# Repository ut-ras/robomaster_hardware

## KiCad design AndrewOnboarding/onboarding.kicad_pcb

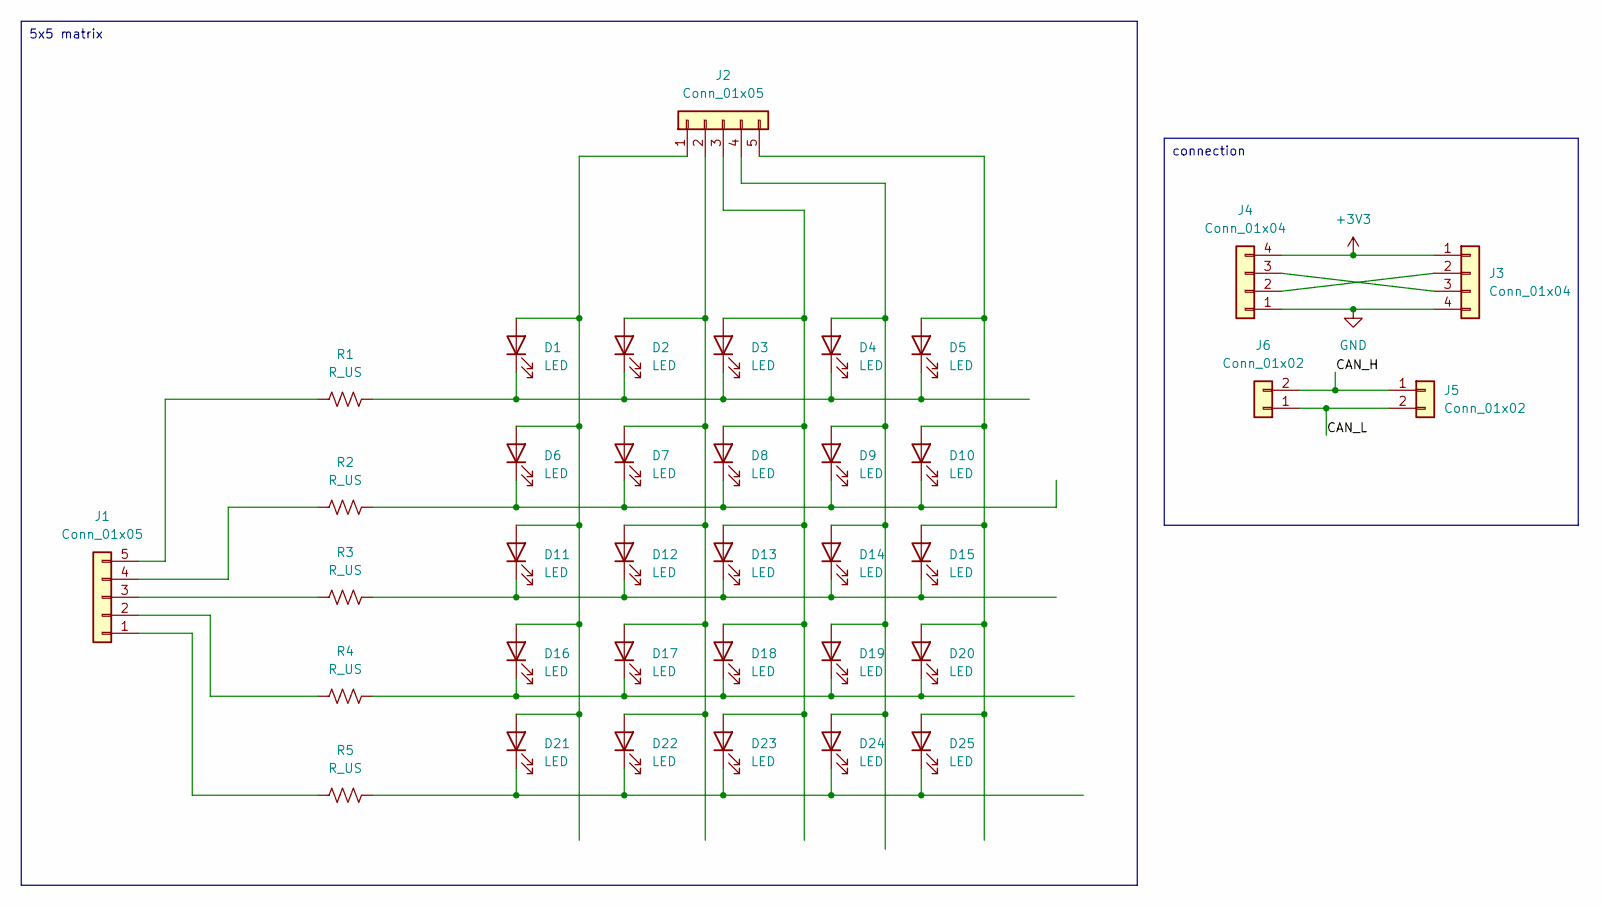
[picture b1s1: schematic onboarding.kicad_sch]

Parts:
D1, D2, D3, D4, D5, D6, D7, D8, D9, D10, D11, D12, D13, D14, D15, D16, D17, D18, D19, D20, D21, D22, D23, D24, D25: LED; LED_D3.0mm
J1, J2: Conn_01x05; PinHeader_1x05_P2.54mm_Vertical
J3, J4: Conn_01x04; JST_NV_B04P-NV_1x04_P5.00mm_Vertical
J5, J6: Conn_01x02; JST_NV_B02P-NV_1x02_P5.00mm_Vertical
R1, R2, R3, R4, R5: R_US; R_Axial_DIN0207_L6.3mm_D2.5mm_P7.62mm_Horizontal

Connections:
+3V3: J3.1, J4.4
/CAN_H: J5.1, J6.2
/CAN_L: J5.2, J6.1
GND: J3.4, J4.1
unnamed: D1.2 (A), D6.2 (A), D11.2 (A), D16.2 (A), D21.2 (A), J2.1
unnamed: D1.1 (K), D2.1 (K), D3.1 (K), D4.1 (K), D5.1 (K), R1.1
unnamed: D5.2 (A), D10.2 (A), D15.2 (A), D20.2 (A), D25.2 (A), J2.5
unnamed: D6.1 (K), D7.1 (K), D8.1 (K), D9.1 (K), D10.1 (K), R2.2
unnamed: D11.1 (K), D12.1 (K), D13.1 (K), D14.1 (K), D15.1 (K), R3.1
unnamed: D2.2 (A), D7.2 (A), D12.2 (A), D17.2 (A), D22.2 (A), J2.2
unnamed: D3.2 (A), D8.2 (A), D13.2 (A), D18.2 (A), D23.2 (A), J2.3
unnamed: D4.2 (A), D9.2 (A), D14.2 (A), D19.2 (A), D24.2 (A), J2.4
unnamed: D16.1 (K), D17.1 (K), D18.1 (K), D19.1 (K), D20.1 (K), R4.1
unnamed: D21.1 (K), D22.1 (K), D23.1 (K), D24.1 (K), D25.1 (K), R5.1
unnamed: J1.1, R5.2
unnamed: J1.2, R4.2
unnamed: J1.3, R3.2
unnamed: J1.4, R2.1
unnamed: J1.5, R1.2
unnamed: J3.2, J4.2
unnamed: J3.3, J4.3

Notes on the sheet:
5x5 matrix
connection

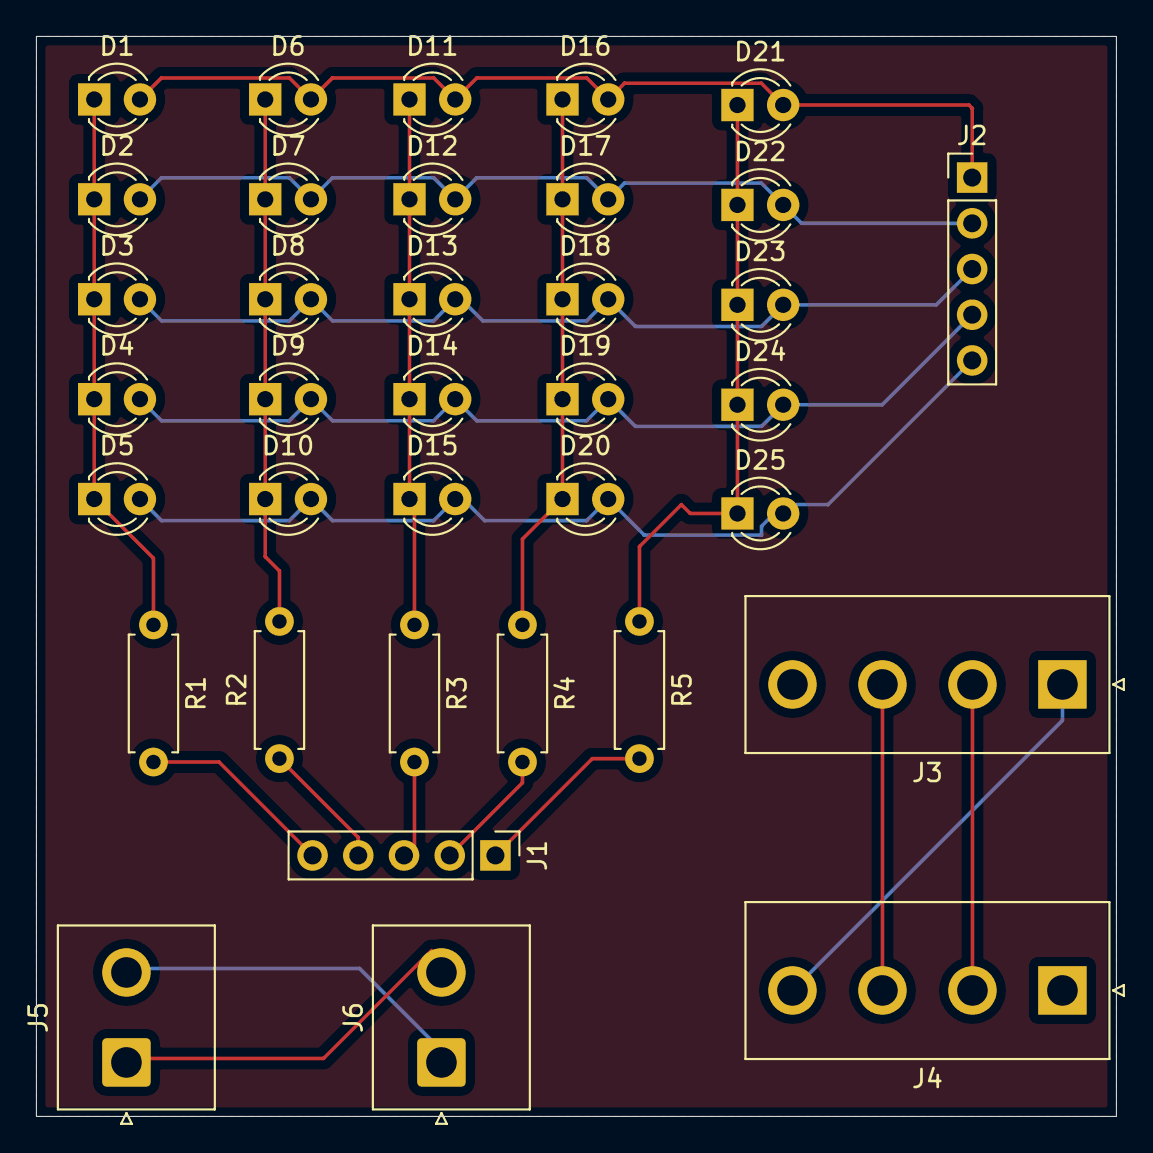
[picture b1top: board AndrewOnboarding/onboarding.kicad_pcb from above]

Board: 2 copper layers, 60.0 x 60.0 mm, 36 parts (0 on the bottom side), 21 nets.

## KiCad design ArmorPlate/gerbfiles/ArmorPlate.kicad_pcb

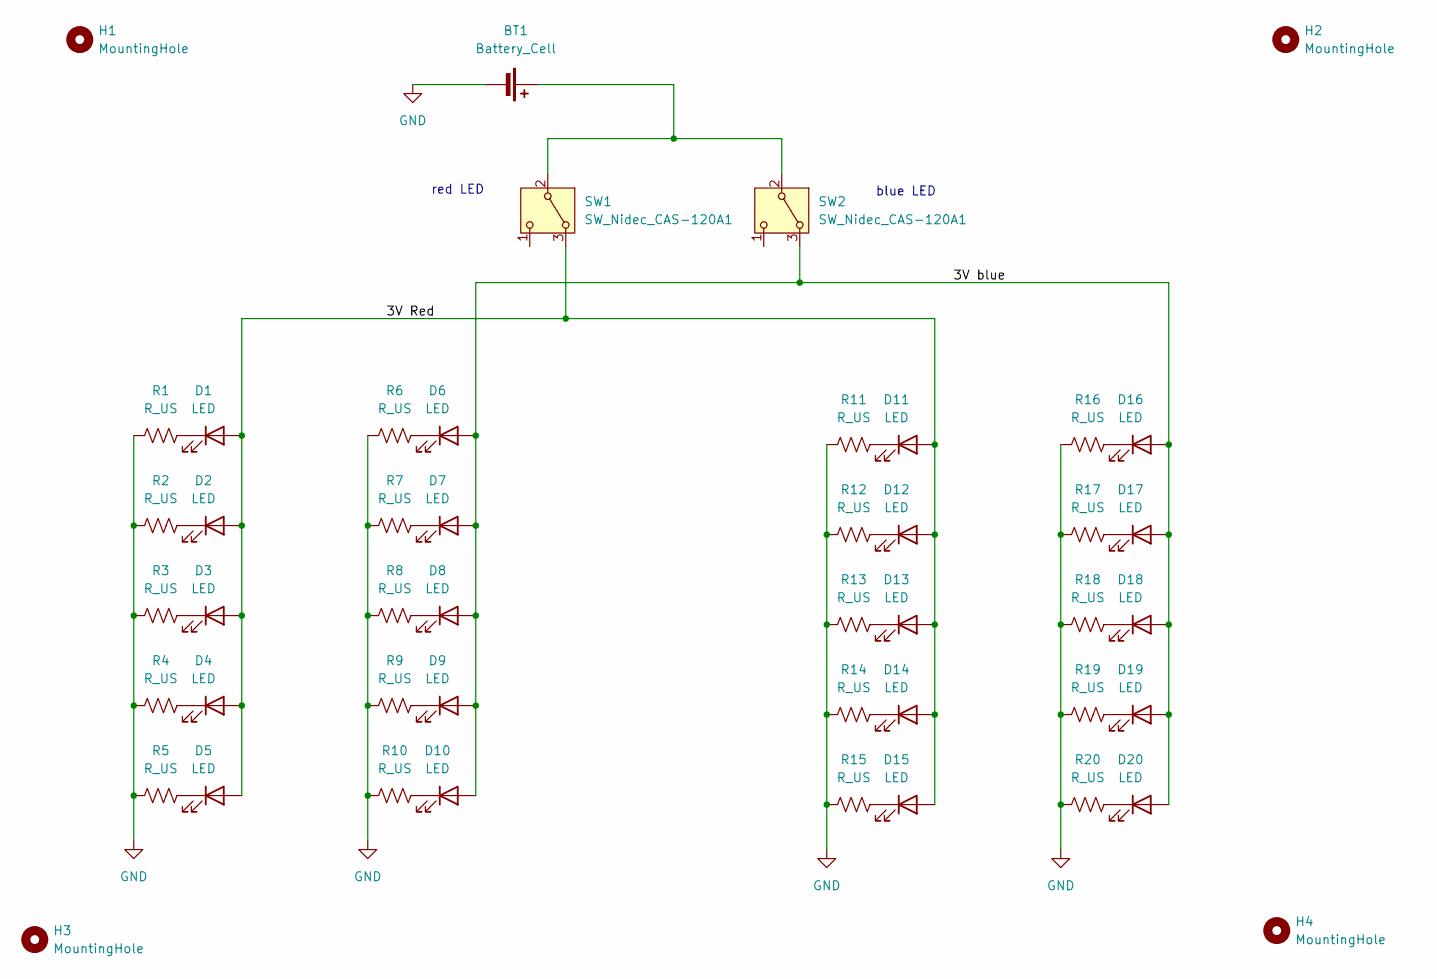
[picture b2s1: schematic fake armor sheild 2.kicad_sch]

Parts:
BT1: Battery_Cell; BatteryHolder_Keystone_2468_2xAAA; Mouser Part Number 613-MN1500-144
D1, D2, D3, D4, D5, D6, D7, D8, D9, D10, D11, D12, D13, D14, D15, D16, D17, D18, D19, D20: LED; LED_0603_1608Metric_Pad1.05x0.95mm_HandSolder; Mouser Part Number 710-150060SS75000
H1, H2, H3, H4: MountingHole; MountingHole_4.5mm
R1, R2, R3, R4, R5, R6, R7, R8, R9, R10, R11, R12, R13, R14, R15, R16, R17, R18, R19, R20: R_US; R_0603_1608Metric_Pad0.98x0.95mm_HandSolder; Mouser Part Number 71-WSLP25125L000FEA
SW1, SW2: SW_Nidec_CAS-120A1; SW_Push_2P1T_Toggle_CK_PVA1xxH1xxxxxxV2; Mouser Part Number 611-181D01000

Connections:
/3V Red: D1.2 (A), D2.2 (A), D3.2 (A), D4.2 (A), D5.2 (A), D11.2 (A), D12.2 (A), D13.2 (A), D14.2 (A), D15.2 (A), SW1.3 (A); also elsewhere on the board
/3V blue: D6.2 (A), D7.2 (A), D8.2 (A), D9.2 (A), D10.2 (A), D16.2 (A), D17.2 (A), D18.2 (A), D19.2 (A), D20.2 (A), SW2.3 (A); also elsewhere on the board
GND: BT1.2 (-), R1.1, R2.1, R3.1, R4.1, R5.1, R6.1, R7.1, R8.1, R9.1, R10.1, R11.1, R12.1, R13.1, R14.1, R15.1, R16.1, R17.1, R18.1, R19.1, R20.1
unnamed 3: BT1.1 (+), SW1.2 (B), SW2.2 (B); also elsewhere on the board
unnamed: D1.1 (K), R1.2
unnamed: D2.1 (K), R2.2
unnamed: D3.1 (K), R3.2
unnamed: D4.1 (K), R4.2
unnamed: D5.1 (K), R5.2
unnamed: D6.1 (K), R6.2
unnamed: D7.1 (K), R7.2
unnamed: D8.1 (K), R8.2
unnamed: D9.1 (K), R9.2
unnamed: D10.1 (K), R10.2
unnamed: D11.1 (K), R11.2
unnamed: D12.1 (K), R12.2
unnamed: D13.1 (K), R13.2
unnamed: D14.1 (K), R14.2
unnamed: D15.1 (K), R15.2
unnamed: D16.1 (K), R16.2
unnamed: D17.1 (K), R17.2
unnamed: D18.1 (K), R18.2
unnamed: D19.1 (K), R19.2
unnamed: D20.1 (K), R20.2

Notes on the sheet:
blue LED
red LED

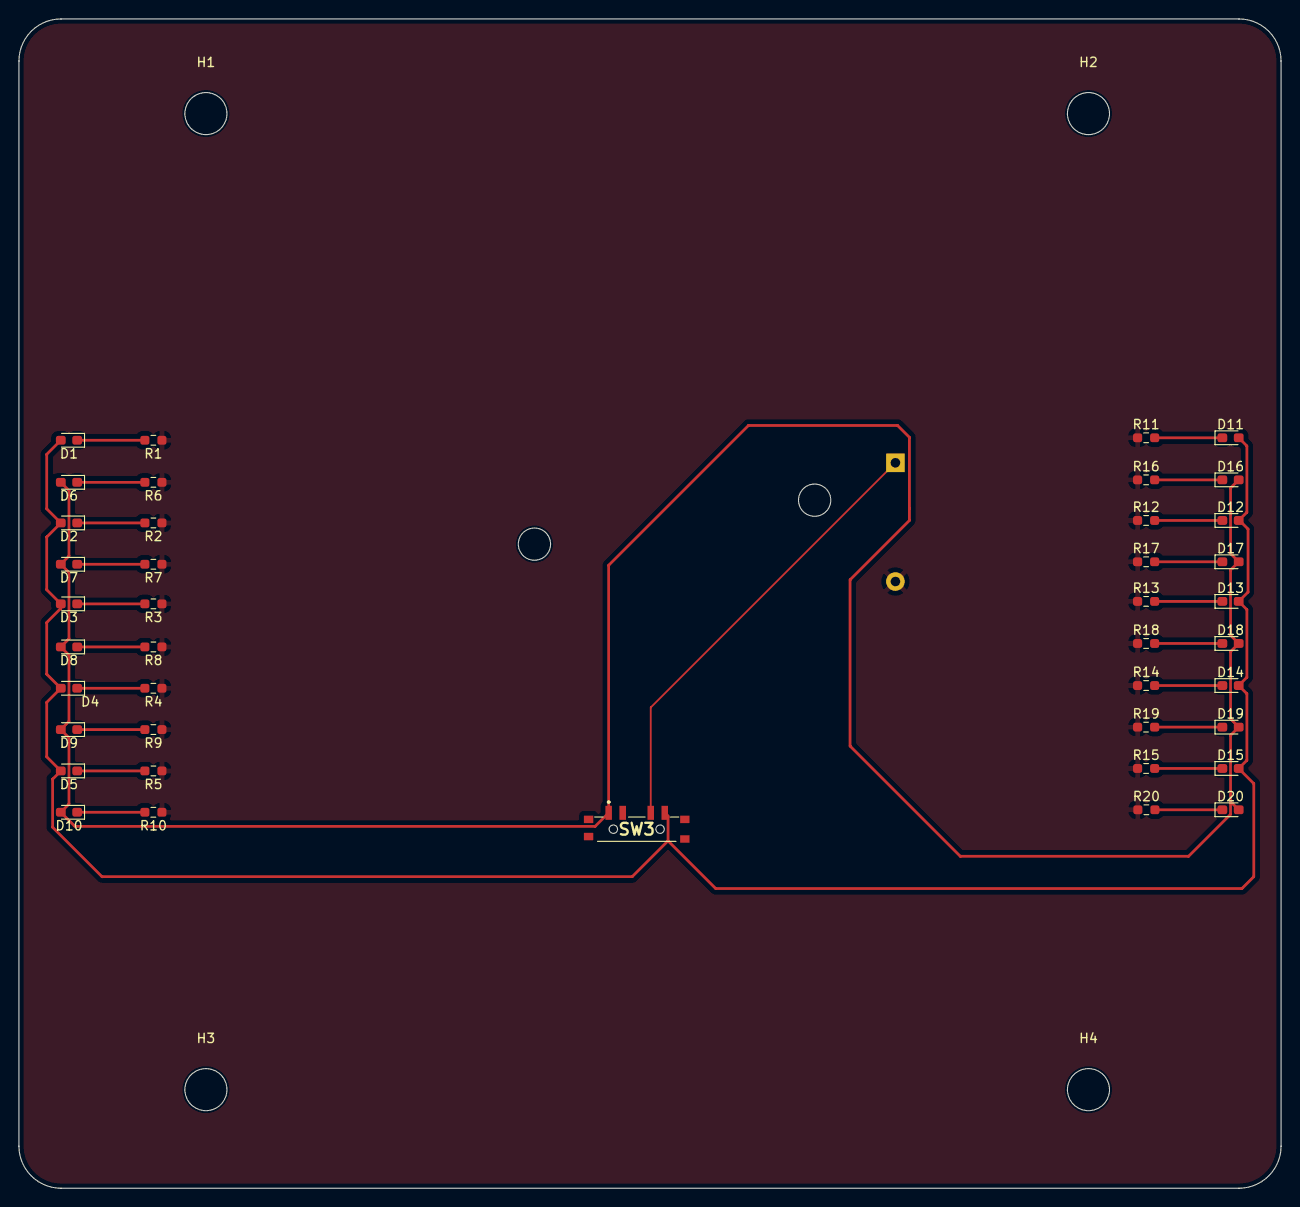
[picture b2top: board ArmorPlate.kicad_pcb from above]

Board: 2 copper layers, 135.0 x 125.1 mm, 46 parts (1 on the bottom side), 24 nets.

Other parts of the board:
SW3: SW_SP3T; EG1315AA

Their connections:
/3V Red: SW3.4; also elsewhere on the board
/3V blue: SW3.1; also elsewhere on the board
unnamed 3: SW3.3; also elsewhere on the board

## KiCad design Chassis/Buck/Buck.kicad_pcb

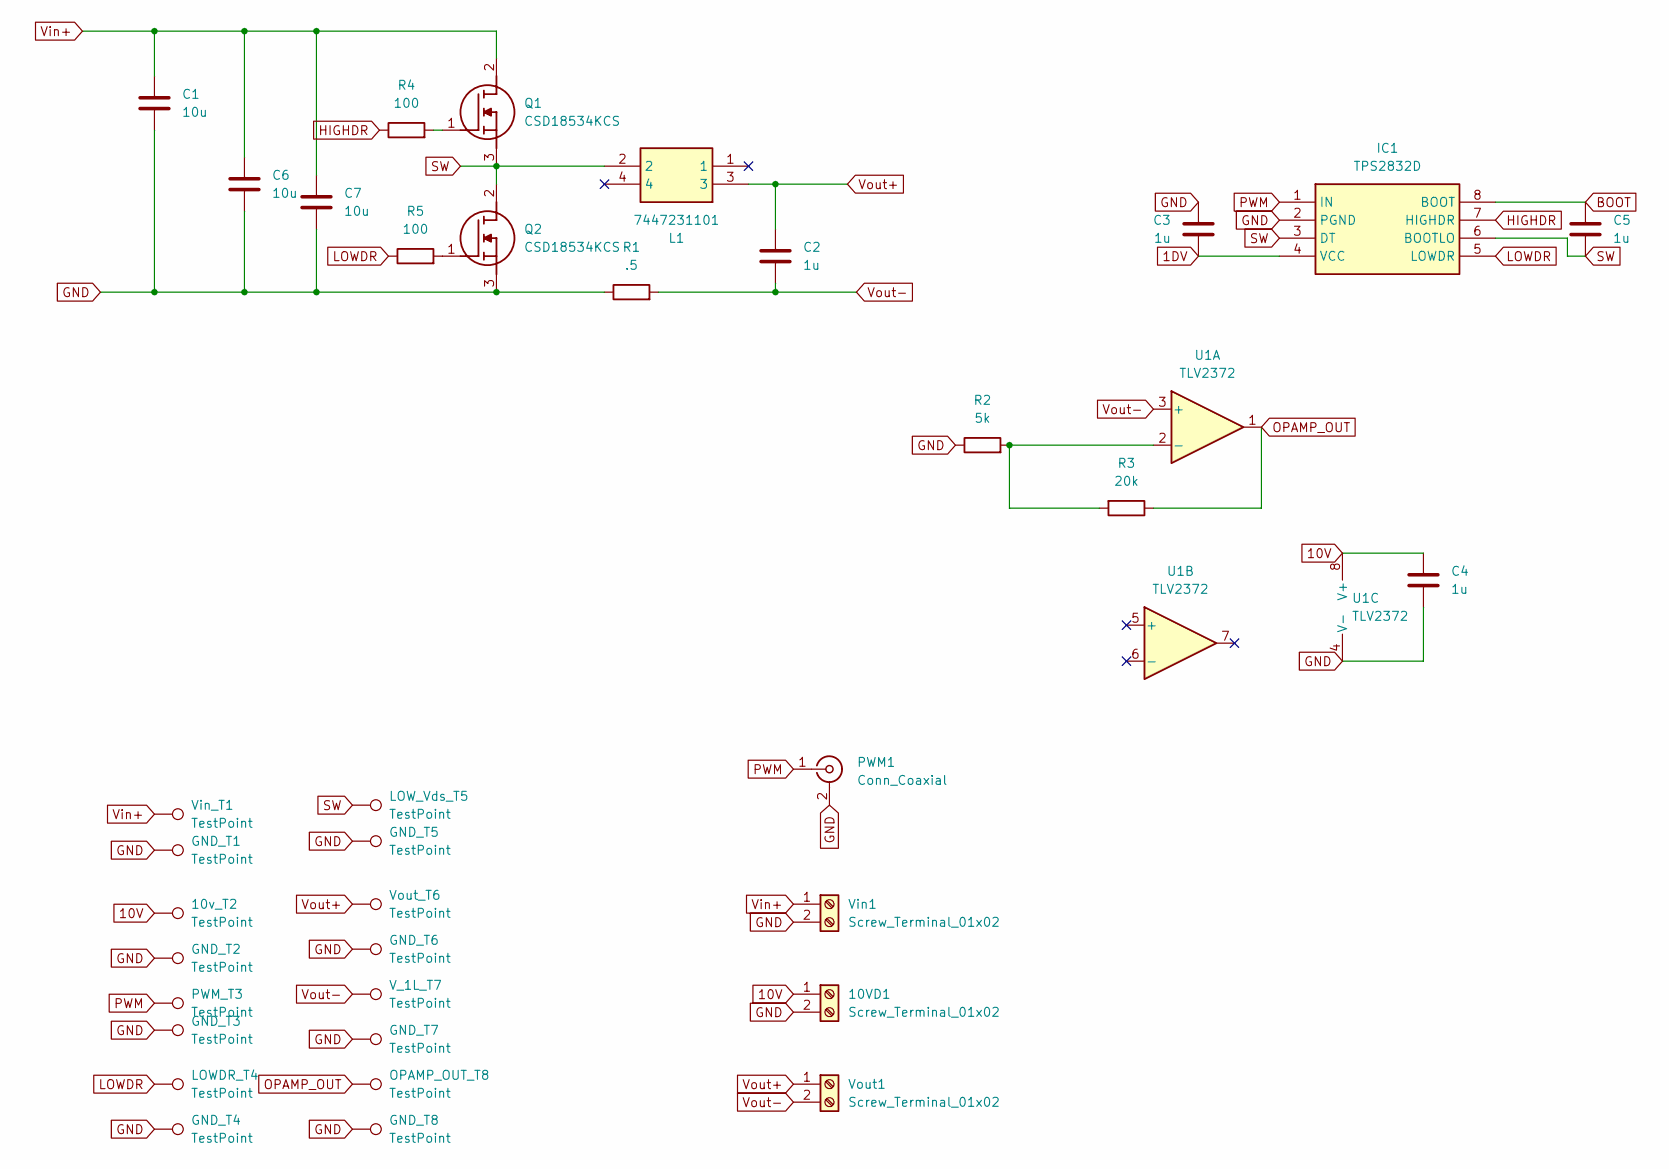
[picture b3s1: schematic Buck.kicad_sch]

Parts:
10VD1: Screw_Terminal_01x02; TO-220-3_Vertical
10v_T2: TestPoint; TestPoint_Keystone_5010-5014_Multipurpose
C1, C6, C7: 10u; C_Disc_D3.8mm_W2.6mm_P2.50mm
C2, C3, C4, C5: 1u; C_Disc_D3.8mm_W2.6mm_P2.50mm
GND_T1, GND_T2, GND_T3, GND_T4, GND_T5, GND_T6, GND_T7, GND_T8: TestPoint; TestPoint_Keystone_5010-5014_Multipurpose
IC1: TPS2832D; SO-8_3.9x4.9mm_P1.27mm; Manufacturer_Part_Number TPS2832D; Mouser Part Number 595-TPS2832D
L1: 7447231101; Manufacturer_Part_Number 7447231101
LOWDR_T4: TestPoint; TestPoint_Keystone_5010-5014_Multipurpose
LOW_Vds_T5: TestPoint; TestPoint_Keystone_5010-5014_Multipurpose
OPAMP_OUT_T8: TestPoint; TestPoint_Keystone_5010-5014_Multipurpose
PWM1: Conn_Coaxial; BNC_Amphenol_B6252HB-NPP3G-50_Horizontal
PWM_T3: TestPoint; TestPoint_Keystone_5010-5014_Multipurpose
Q1, Q2: CSD18534KCS; TO-220-3_Vertical; Manufacturer_Part_Number CSD18534KCS; Mouser Part Number 595-CSD18534KCS
R1: .5; R_Axial_DIN0922_L20.0mm_D9.0mm_P30.48mm_Horizontal
R2: 5k; R_Axial_DIN0207_L6.3mm_D2.5mm_P10.16mm_Horizontal
R3: 20k; R_Axial_DIN0207_L6.3mm_D2.5mm_P10.16mm_Horizontal
R4, R5: 100; R_Axial_DIN0207_L6.3mm_D2.5mm_P10.16mm_Horizontal
U1: TLV2372; SO-8_3.9x4.9mm_P1.27mm
V_1L_T7: TestPoint; TestPoint_Keystone_5010-5014_Multipurpose
Vin1: Screw_Terminal_01x02; PhoenixContact_MSTBA_2,5_2-G_1x02_P5.00mm_Horizontal
Vin_T1: TestPoint; TestPoint_Keystone_5010-5014_Multipurpose
Vout1: Screw_Terminal_01x02; PhoenixContact_MSTBA_2,5_2-G_1x02_P5.00mm_Horizontal
Vout_T6: TestPoint; TestPoint_Keystone_5010-5014_Multipurpose

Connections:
1DV: C3.2, IC1.4 (VCC)
10V: 10VD1.1, 10v_T2.1, C4.1, U1.8 (V+)
BOOT: C5.1, IC1.8 (BOOT)
GND: 10VD1.2, C1.1, C3.1, C4.2, C6.2, C7.2, GND_T1.1, GND_T2.1, GND_T3.1, GND_T4.1, GND_T5.1, GND_T6.1, GND_T7.1, GND_T8.1, IC1.2 (PGND), PWM1.2 (Ext), Q2.3 (S), R1.1, R2.1, U1.4 (V-), Vin1.2
HIGHDR: IC1.7 (HIGHDR), R4.1
LOWDR: IC1.5 (LOWDR), LOWDR_T4.1, R5.1
unnamed: Q1.1 (G), R4.2
unnamed: Q2.1 (G), R5.2
unnamed: R2.2, R3.2, U1.2 (-)
OPAMP_OUT: OPAMP_OUT_T8.1, R3.1, U1.1
PWM: IC1.1 (IN), PWM1.1 (In), PWM_T3.1
SW: C5.2, IC1.3 (DT), IC1.6 (BOOTLO), L1.2, LOW_Vds_T5.1, Q1.3 (S), Q2.2 (D)
Vin+: C1.2, C6.1, C7.1, Q1.2 (D), Vin1.1, Vin_T1.1
Vout+: C2.1, L1.3, Vout1.1, Vout_T6.1
Vout-: C2.2, R1.2, U1.3 (+), V_1L_T7.1, Vout1.2

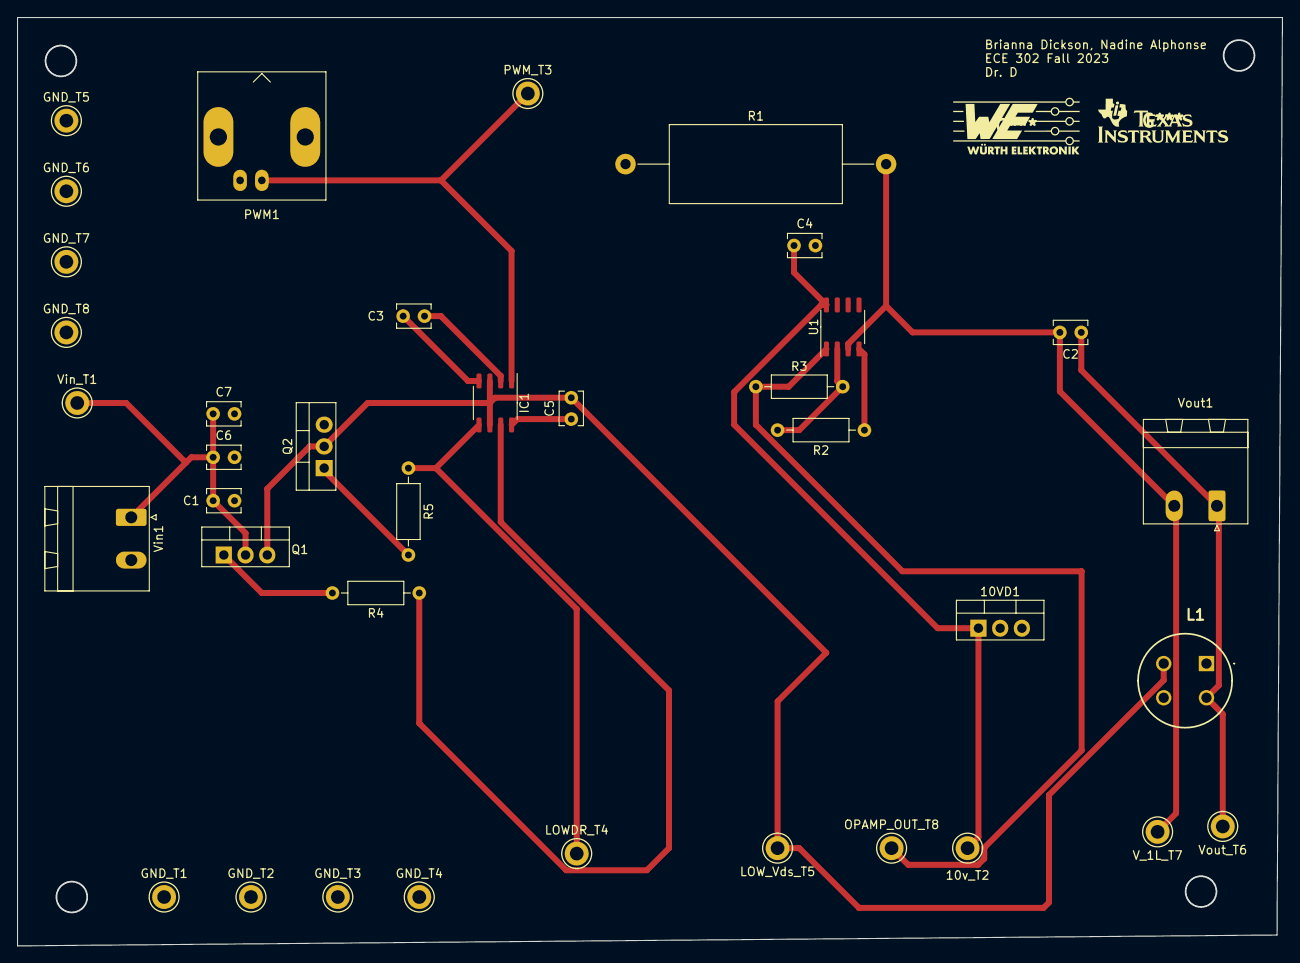
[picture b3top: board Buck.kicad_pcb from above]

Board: 2 copper layers, 148.0 x 108.6 mm, 37 parts (0 on the bottom side), 15 nets.

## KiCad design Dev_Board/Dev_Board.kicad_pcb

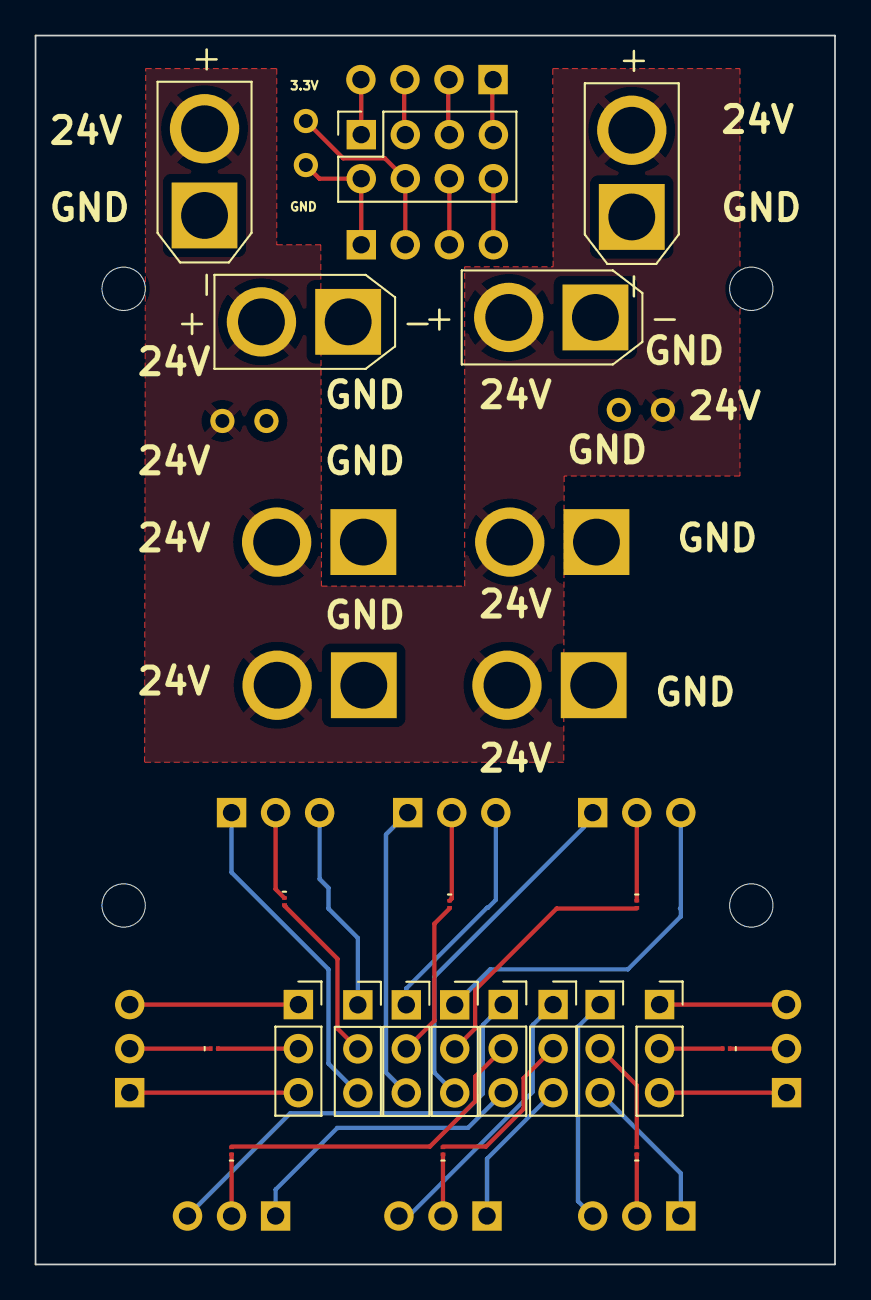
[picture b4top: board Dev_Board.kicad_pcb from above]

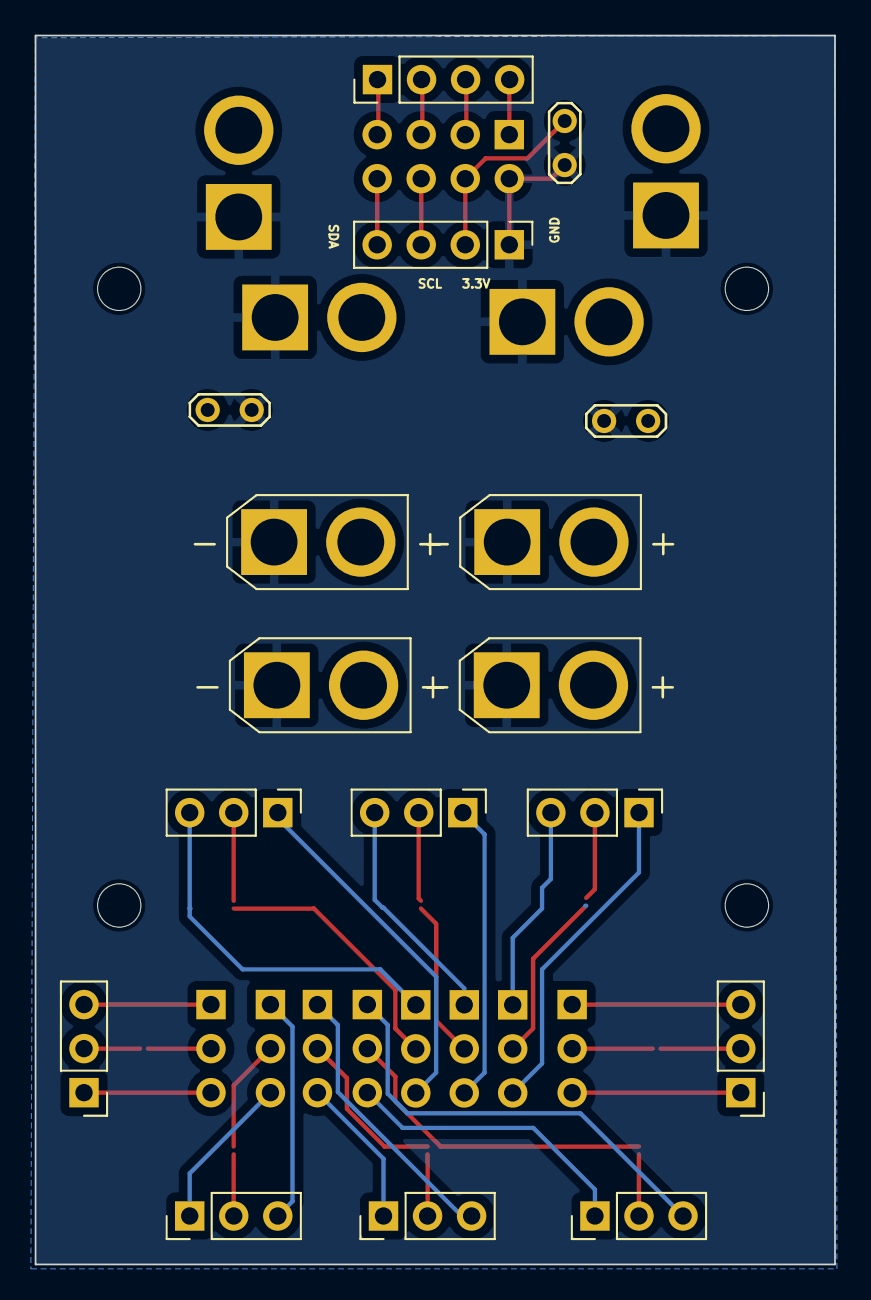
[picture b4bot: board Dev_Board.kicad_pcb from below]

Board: 2 copper layers, 46.1 x 70.9 mm, 42 parts (17 on the bottom side), 40 nets.

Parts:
D1, D4, D7, D11, D14, D17, D20, D23: D; Nexperia_DSN0603-2_0.6x0.3mm_P0.4mm
DBUS1: Conn_01x03; PinSocket_1x03_P2.54mm_Vertical
H1, H2, H3, H4: MountingHole; MountingHole_2.5mm
IO_Port1: Conn_02x04_Odd_Even; PinSocket_2x04_P2.54mm_Vertical
In_Port1, In_Port2: Conn_01x02; AMASS_XT30U-F_1x02_P5.0mm_Vertical
J1, J2: Conn_01x04; PinHeader_1x04_P2.54mm_Vertical
Out_Port1, Out_Port2, Out_Port3, Out_Port4, Out_Port6, Out_Port8: Conn_01x02; AMASS_XT30U-F_1x02_P5.0mm_Vertical
PWM_R1, PWM_R2, PWM_R3, PWM_R4, PWM_R5, PWM_R6, PWM_R7: Conn_01x03; PinSocket_1x03_P2.54mm_Vertical
PWM_R8, PWM_R9, PWM_R10, PWM_R11, PWM_R12, PWM_R13, PWM_R14, PWM_R15: Conn_01x03; PinHeader_1x03_P2.54mm_Vertical
TP1, TP4, TP5: TestPoint_2Pole; TestPoint_2Pads_Pitch2.54mm_Drill0.8mm

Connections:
+3.3V: IO_Port1.4, J2.2, TP1.2
+24V: In_Port1.2, In_Port2.2, Out_Port1.2, Out_Port2.2, Out_Port3.2, Out_Port4.2, Out_Port6.2, Out_Port8.2, TP4.2, TP5.2
/A2: PWM_R2.1, PWM_R9.3
/A3: PWM_R3.1, PWM_R10.3
/A4: PWM_R4.1, PWM_R11.3
/A5: PWM_R5.1, PWM_R12.3
/A6: PWM_R6.1, PWM_R13.3
/B1 (5V): D1.2 (A), PWM_R1.2
/B3: D7.2 (A), PWM_R3.2
/B4: D11.2 (A), PWM_R4.2
/B5: D14.2 (A), PWM_R5.2
/B6: D17.2 (A), PWM_R6.2
/C3: PWM_R3.3, PWM_R10.1
/C4: PWM_R4.3, PWM_R11.1
/C5: PWM_R5.3, PWM_R12.1
/C8: DBUS1.3, PWM_R15.1
/I2C2_SCL: IO_Port1.6, J2.3
/I2C2_SDA: IO_Port1.8, J2.4
/SPI2_CLK: IO_Port1.3, J1.3
/SPI2_CS: IO_Port1.1, J1.4
/SPI2_MOSI: IO_Port1.5, J1.2
GND: IO_Port1.2, In_Port1.1, In_Port2.1, J2.1, Out_Port1.1, Out_Port2.1, Out_Port3.1, Out_Port4.1, Out_Port6.1, Out_Port8.1, TP1.1, TP4.1, TP5.1
unnamed: D1.1 (K), PWM_R8.2
unnamed: D4.2 (A), PWM_R2.2
unnamed: D4.1 (K), PWM_R9.2
unnamed: D7.1 (K), PWM_R10.2
unnamed: D11.1 (K), PWM_R11.2
unnamed: D14.1 (K), PWM_R12.2
unnamed: D17.1 (K), PWM_R13.2
unnamed: D20.2 (A), PWM_R7.2
unnamed: D20.1 (K), PWM_R14.2
unnamed: D23.2 (A), DBUS1.2
unnamed: D23.1 (K), PWM_R15.2
unnamed: DBUS1.1, PWM_R15.3
unnamed: PWM_R1.1, PWM_R8.3
unnamed: PWM_R1.3, PWM_R8.1
unnamed: PWM_R2.3, PWM_R9.1
unnamed: PWM_R6.3, PWM_R13.1
unnamed: PWM_R7.3, PWM_R14.1
unnamed: PWM_R7.1, PWM_R14.3

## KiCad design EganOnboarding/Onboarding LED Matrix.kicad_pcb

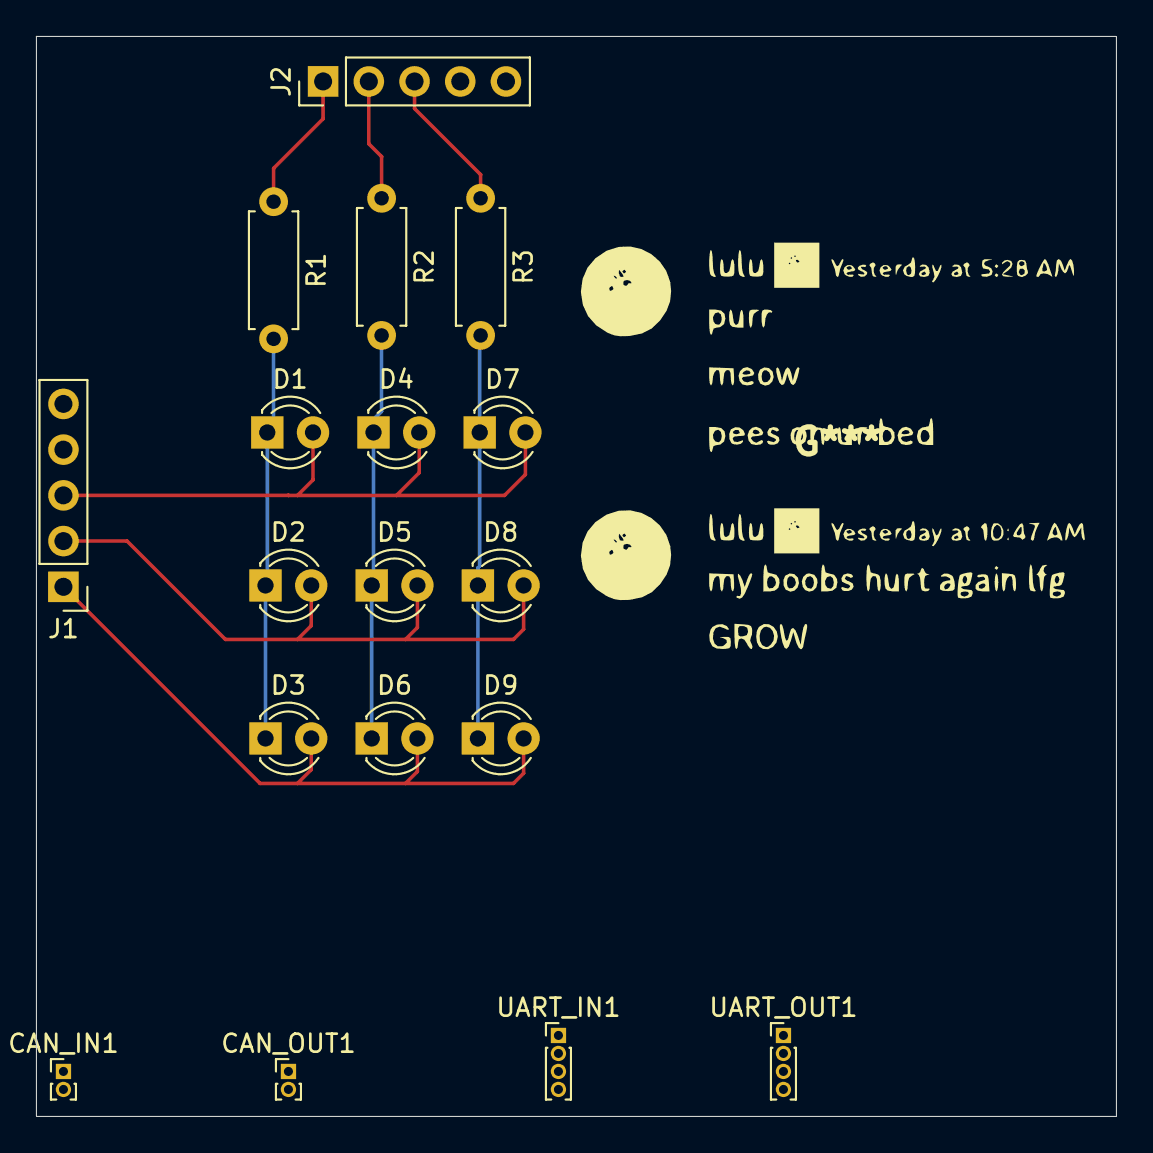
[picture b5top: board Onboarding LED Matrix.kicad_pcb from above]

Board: 2 copper layers, 60.0 x 60.0 mm, 18 parts (0 on the bottom side), 9 nets.

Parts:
CAN_IN1: Conn_01x02_Pin; PinHeader_1x02_P1.00mm_Vertical
CAN_OUT1: Conn_01x02_Pin; PinHeader_1x02_P1.00mm_Vertical
D1, D2, D3, D4, D5, D6, D7, D8, D9: LED; LED_D3.0mm
J1, J2: Conn_01x05_Pin; PinHeader_1x05_P2.54mm_Vertical
R1, R2, R3: R; R_Axial_DIN0207_L6.3mm_D2.5mm_P7.62mm_Horizontal
UART_IN1: Conn_01x04_Pin; PinHeader_1x04_P1.00mm_Vertical
UART_OUT1: Conn_01x04_Pin; PinHeader_1x04_P1.00mm_Vertical

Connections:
unnamed: D1.2 (A), D4.2 (A), D7.2 (A), J1.3
unnamed: D1.1 (K), D2.1 (K), D3.1 (K), R1.2
unnamed: D2.2 (A), D5.2 (A), D8.2 (A), J1.2
unnamed: D3.2 (A), D6.2 (A), D9.2 (A), J1.1
unnamed: D4.1 (K), D5.1 (K), D6.1 (K), R2.2
unnamed: D7.1 (K), D8.1 (K), D9.1 (K), R3.2
unnamed: J2.1, R1.1
unnamed: J2.2, R2.1
unnamed: J2.3, R3.1

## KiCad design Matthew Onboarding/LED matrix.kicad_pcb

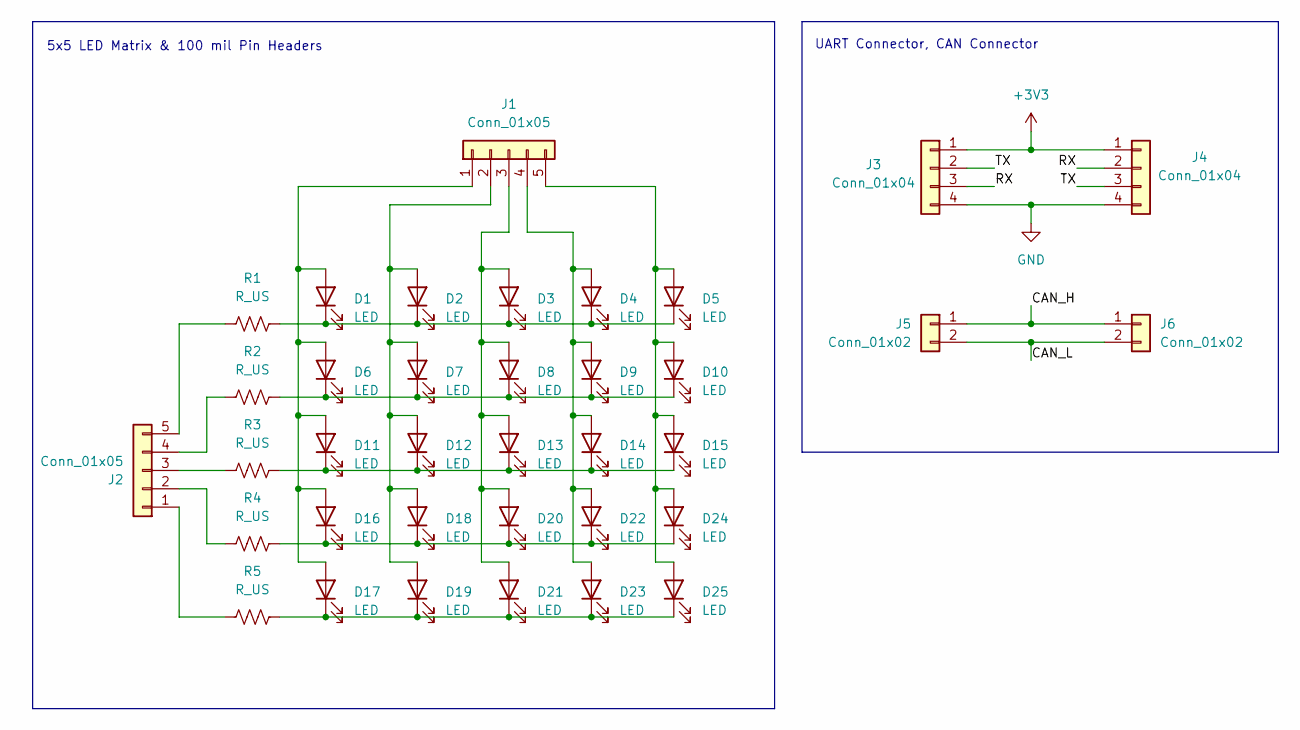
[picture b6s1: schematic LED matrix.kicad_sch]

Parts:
D1, D2, D3, D4, D5, D6, D7, D8, D9, D10, D11, D12, D13, D14, D15, D16, D17, D18, D19, D20, D21, D22, D23, D24, D25: LED; LED_D3.0mm
J1, J2: Conn_01x05; PinSocket_1x05_P2.54mm_Vertical
J3, J4: Conn_01x04; JST_GH_BM04B-GHS-TBT_1x04-1MP_P1.25mm_Vertical
J5, J6: Conn_01x02; JST_GH_BM02B-GHS-TBT_1x02-1MP_P1.25mm_Vertical
R1, R2, R3, R4, R5: R_US; R_Axial_DIN0207_L6.3mm_D2.5mm_P7.62mm_Horizontal

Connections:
+3V3: J3.1, J4.1
/CAN_H: J5.1, J6.1
/CAN_L: J5.2, J6.2
/RX: J3.3, J4.2
/TX: J3.2, J4.3
GND: J3.4, J4.4
unnamed: D1.2 (A), D6.2 (A), D11.2 (A), D16.2 (A), D17.2 (A), J1.1
unnamed: D1.1 (K), D2.1 (K), D3.1 (K), D4.1 (K), D5.1 (K), R1.2
unnamed: D5.2 (A), D10.2 (A), D15.2 (A), D24.2 (A), D25.2 (A), J1.5
unnamed: D6.1 (K), D7.1 (K), D8.1 (K), D9.1 (K), D10.1 (K), R2.2
unnamed: D11.1 (K), D12.1 (K), D13.1 (K), D14.1 (K), D15.1 (K), R3.2
unnamed: D2.2 (A), D7.2 (A), D12.2 (A), D18.2 (A), D19.2 (A), J1.2
unnamed: D3.2 (A), D8.2 (A), D13.2 (A), D20.2 (A), D21.2 (A), J1.3
unnamed: D4.2 (A), D9.2 (A), D14.2 (A), D22.2 (A), D23.2 (A), J1.4
unnamed: D16.1 (K), D18.1 (K), D20.1 (K), D22.1 (K), D24.1 (K), R4.2
unnamed: D17.1 (K), D19.1 (K), D21.1 (K), D23.1 (K), D25.1 (K), R5.2
unnamed: J2.1, R5.1
unnamed: J2.2, R4.1
unnamed: J2.3, R3.1
unnamed: J2.4, R2.1
unnamed: J2.5, R1.1

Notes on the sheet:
UART Connector, CAN Connector
5x5 LED Matrix & 100 mil Pin Headers

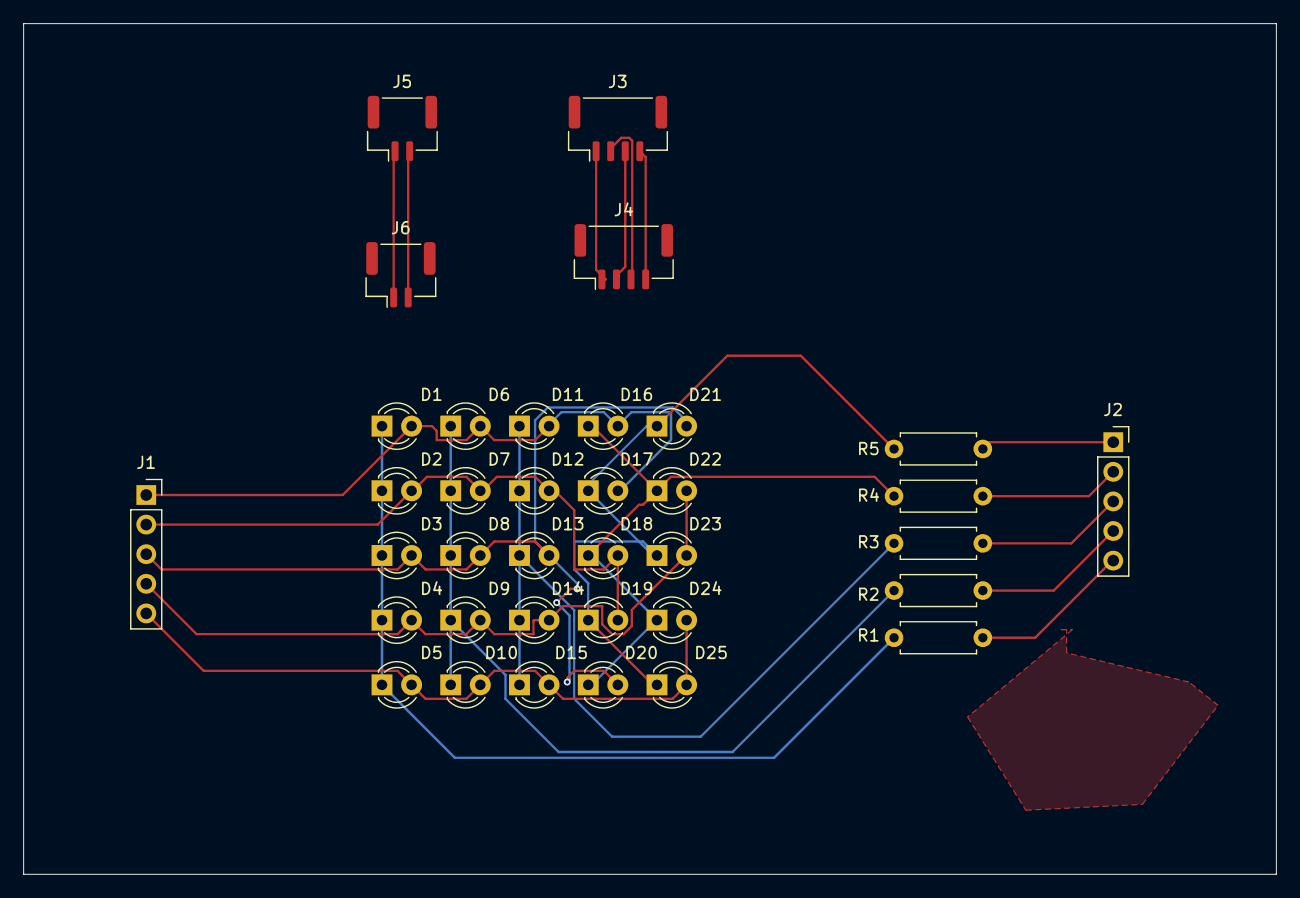
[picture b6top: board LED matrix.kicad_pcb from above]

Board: 2 copper layers, 107.5 x 73.0 mm, 36 parts (0 on the bottom side), 21 nets.
